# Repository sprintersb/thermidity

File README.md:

# Thermidity

AVR MCU based battery powered thermometer and hygrometer with e-ink display.  
Focus is on stable, accurate measurements and low power consumption. 
And of course on a nice, simple display.

The project is based on [avrink](https://github.com/gitdode/avrink) and uses the
following components:

* MCU AVR ATmega328P
* Thermistor NTC 100kΩ 0.1°C
* Humidity Sensor HIH-5030
* E-Ink display Adafruit Monochrome 2.13" 250x122
    * Driver SSD1680
    * SRAM 23K640
    * SD Card Reader (not used)
 
Thanks to https://github.com/sprintersb for helping me to improve the code and making it more efficient!

## Accuracy

AD conversion is done with 16x oversampling, yielding 12-bit virtual resolution 
with the 10-bit ADC, provided the signal contains some noise.

Each time measurements were taken, a moving average is updated which is used to 
calculate and display temperature, humidity and battery voltage.

A precision thermistor and precision low-voltage humidity sensor are used:

| Component  | Accuracy |
|------------|---------:|
| Thermistor |  ¹±0.1°C |
| HIH-5030   |    ±3%RH |

¹Series resistor 0.1% tolerance

## Power Consumption

Estimated average power consumption is about 90µA when measuring every 32 
seconds and updating the display once in about 5 minutes, hopefully giving an
operating time of at least 12 months with 3 AAA batteries (1100 mAh, 6% 
self-discharge). 

The consumption of each component at 3.8V and 22°C is about:

| Component  | Data Sheet | Measured |
|------------|-----------:|---------:|
| ATmega328P |     ¹4.2µA |    4.5µA |
| Thermistor |        N/A |     24µA |
| HIH-5030   |     ²200µA |    211µA |
| V-Divider  |        N/A |      2µA |
| Display    |       ³N/A |     14µA |

¹VCC = 3V, power-down sleep mode  
²VCC = 3.3V  
³Display in deep sleep mode + SRAM + SD Card Reader + Bus Transceiver  

Between taking measurements, the MCU is set to power-down sleep mode with the
watchdog used as wake-up source. Additionally, the thermistor and humidity 
sensor are powered off and between display updates, the display is set to deep 
sleep mode. Power consumption (measured) then is about 19µA at 3.8V for MCU 
and display.  

When measuring temperature, humidity and battery voltage in ADC noise reduction 
mode, consumption seems to be somewhere around 2mA for 6ms, plus a brief 
additional MCU awake period for updating the moving average with measured 
values. Before measuring, the sensors are powered on and given 100ms to settle, 
consuming about 240µA.

When updating the display, consumption is at around 6mA for about 3 seconds. 
Before that, the MCU has to calculate and format the average measurements and 
buffer the frame in SRAM.

The display is updated in fast update mode, taking 1.5s instead of 3s for full 
update mode, saving a considerable amount of power. To avoid ghosting effects, 
every 10th update is a full update.

When no measurement has changed, the display is not updated at all to extend its 
lifetime and to save more power.

Below the cutoff voltage of 3.0V, the watchdog is disabled to stop measuring and
updating the display, to at least delay total discharge of the batteries.
Consumption of the MCU then is at about 1µA and 19µA of the display.

The clock of unused modules TWI, all three timers and USART is switched off to 
reduce power consumption.

Disabling the ADC between measurements and the SPI between display updates both 
contributes to a significant reduction of power consumption. With an enabled SPI, 
consumption of the display including its peripheral is extremely unstable and 
varies between some tens of microamps and several milliamps. When driving the 
enable pin of the display low, consumption is stable at about 60µA. When not 
driving the enable pin low and disabling SPI (driving SCK pin low) consumption 
is at about 14µA.

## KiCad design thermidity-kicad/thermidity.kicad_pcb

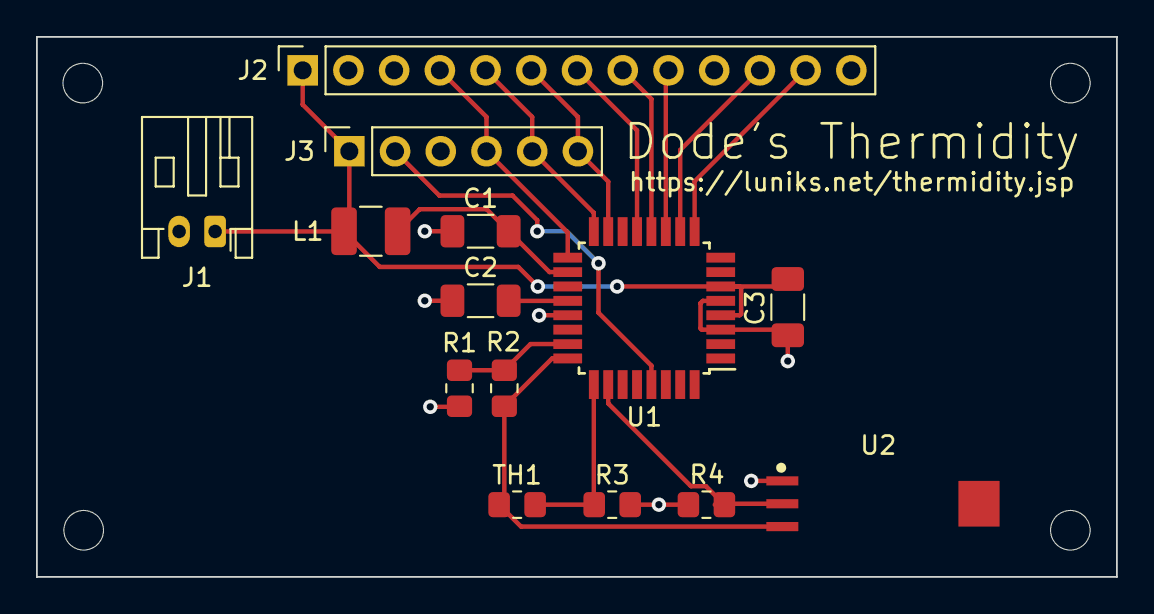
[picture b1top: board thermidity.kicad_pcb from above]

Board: 2 copper layers, 60.0 x 30.0 mm, 18 parts (0 on the bottom side), 16 nets.

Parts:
C1, C3: 100nF; C_1206_3216Metric_Pad1.33x1.80mm_HandSolder
C2: 1nF; C_1206_3216Metric_Pad1.33x1.80mm_HandSolder
H1, H2, H3, H4: M2; MountingHole_2.2mm_M2
J1: Battery; JST_PH_S2B-PH-K_1x02_P2.00mm_Horizontal
J2: Display; PinSocket_1x13_P2.54mm_Vertical
J3: ISP; PinSocket_1x06_P2.54mm_Vertical
L1: 10uH; L_1210_3225Metric_Pad1.42x2.65mm_HandSolder
R1: 300K; R_0805_2012Metric_Pad1.20x1.40mm_HandSolder
R2: 1.2M; R_0805_2012Metric_Pad1.20x1.40mm_HandSolder
R3: 100k 0.1%; R_0805_2012Metric_Pad1.20x1.40mm_HandSolder
R4: 65k; R_0805_2012Metric_Pad1.20x1.40mm_HandSolder
TH1: NTC 100k 0.1°C; R_0805_2012Metric_Pad1.20x1.40mm_HandSolder
U1: ATmega328P; TQFP-32_7x7mm_P0.8mm
U2: HIH-5030; HONEYWELL_HIH-5030-001

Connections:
+BATT: C3.2, J1.1, J2.1 (VIN), J3.1 (VCC), L1.1, U1.4 (VCC), U1.6 (VCC)
GND: C1.1, C2.1, C3.1, J1.2, J2.3 (GND), J3.3 (GND), R1.2, R3.2, R4.2, U1.3 (GND), U1.5 (GND), U1.21 (GND), U2.1 (-VE)
unnamed: C1.2, L1.2, U1.18 (AVCC)
unnamed: J2.4 (SCK), J3.4 (SCK), U1.17 (PB5)
unnamed: J2.5 (MISO), J3.5 (MISO), U1.16 (PB4)
unnamed: J2.6 (MOSI), J3.6 (MOSI), U1.15 (PB3)
unnamed: J2.7 (ECS), U1.13 (PB1)
unnamed: J2.8 (D/C), U1.12 (PB0)
unnamed: J2.9 (SRCS), U1.11 (PD7)
unnamed: J2.11 (RST), U1.10 (PD6)
unnamed: J2.12 (BUSY), U1.9 (PD5)
unnamed: J3.2 (RESET), U1.29 (~RESET/PC6)
unnamed: R1.1, R2.2, U1.23 (PC0)
unnamed: R2.1, TH1.1, U1.24 (PC1), U2.3 (+VE)
unnamed: R4.1, U1.26 (PC3), U2.2 (OUT)
unnamed: R3.1, TH1.2, U1.25 (PC2)

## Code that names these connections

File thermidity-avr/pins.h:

/* 
 * File:   pins.h
 * Author: torsten.roemer@luniks.net
 *
 * Created on 1. April 2023, 19:25
 */

#ifndef PINS_H
#define PINS_H

#include <avr/io.h>

/* Vref and Sensors */
#define DDR_SENS  DDRC
#define PORT_SENS PORTC
#define PIN_REF   PC0
#define PIN_TMP   PC2
#define PIN_RH    PC3
#define PIN_BAT   PC1

/* SPI */
#define DDR_SPI   DDRB
#define PORT_SPI  PORTB
#define PIN_SS    PB2
#define PIN_MOSI  PB3
#define PIN_MISO  PB4
#define PIN_SCK   PB5

/* SRAM */
#define DDR_SSPI  DDRD
#define PORT_SSPI PORTD
#define PIN_SRCS  PD7 // SRAM chip select

/* Display */
#define DDR_DSPI  DDRB
#define PORT_DSPI PORTB
#define PIN_ECS   PB1 // display chip select
#define PIN_DC    PB0 // display data/command

#define DDR_DISP  DDRD
#define PORT_DISP PORTD
#define PINP_DISP PIND
#define PIN_RST   PD6 // display reset
#define PIN_BUSY  PD5 // display busy

#endif /* PINS_H */

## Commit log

2023-05-04 add configurations.xml
2023-05-04 add build action and README.md
2023-05-04 improve rounding
2023-05-05 list components
2023-05-09 change and fix intervals of measuring and displaying values
2023-05-10 improve image quality
2023-05-12 improvements regarding measuring
    - measure more frequently
    - reduce weight of EWMA to 3:1
    - simplify update of EWMA
2023-05-14 do not update display when measurements did not change (#4)
2023-05-17 use 3.0V voltage reference for AREF, measure battery voltage (#6)
2023-05-17 use 3.0V voltage reference for AREF, measure battery voltage
2023-05-18 display a battery level symbol (#8)
2023-05-18 save power with watchdog: reduces from 7 to 1.1 mA, but still too much (#9)
    - use watchdog to wake up the controller every 8 seconds
    - set to power save mode
    - use ADC noise reduction mode for conversion
2023-05-18 fix comment
2023-05-18 allow some time to settle before making the first measurement
2023-05-18 wdt_reset() is not necessary
2023-05-18 improve bitmap
2023-05-19 stop the clock of unused modules to reduce power consumption
2023-05-21 move to subdir
2023-05-21 add FreeCAD subproject for frame
2023-05-21 add initial schematic
2023-05-21 move KiCad project
2023-05-21 move LICENSE and README.md
2023-05-21 move and adjust build.yml
2023-05-22 fix build.yml
2023-05-22 fix compiler warnings/notes
2023-05-22 remove 100nF cap from humidity sensor
2023-05-23 update schematic
2023-05-23 fix merge conflict
2023-05-23 use timer2 to wake up from power save mode (#11)
    - seems to consume less power than using watchdog
    - allows to be clocked by external watch crystal and use even less power
2023-05-23 formatting
2023-05-25 Power save mode with asynchronous timer2 clocked from external 32kHz watch crystal (#12)
    * use timer2 with external crystal - 0.6 mA, already quite good
    * disable ADC before going to sleep - saves another 200 uA
    * update README, add crystal to schematic
2023-05-25 fix typo
2023-05-29 improve circuit, update schematic, initial PCB, adjust pins
2023-05-31 Use watchdog to wake up MCU from sleep mode every second (#13)
    - avoids increasing current draw with 8 second interval
    - remove unnecessary checks
    - giving the ADC some time after sleep mode is not necessary
2023-05-31 minor schematic layout changes
2023-06-01 try to save some more power
    - use power-down sleep mode
    - stop timer2 clock as well
2023-06-01 update README, schematic + PCB (remove crystal)
2023-06-02 improve PCB, add comments
2023-06-02 improve README
2023-06-04 improve PCB
2023-06-04 trying to finalize...
2023-06-06 put back ground area and add vias for better connection
2023-06-06 use print instead of SMD for JST connector
2023-06-07 power off vref during idle time reducing consumption from 400uA to 43uA
    - power off vref including humidity sensor
    - add serial resistor to reduce charge current
    - fix pin initialization
2023-06-09 correct handling of variables > 8 bit shared between ISR and main execution path
2023-06-11 ratiometric measurement of humidity (#16)
    - removed voltage refererence
    - TMP36 to be replaced by thermistor (currently dependent on battery voltage)
    - battery voltage measurement should use internal 1.1 Vref (does not need to be accurate)
    - update schematic and README
    - update PCB
    - measure battery voltage using internal 1.1V reference
2023-06-11 remove the 1pF capacitor between AREF and GND
    - takes ~125us to discharge after switching from AVCC to internal 1.1 voltage reference and for the reference to settle
    - shouldn't be necessary and hopefully the 16x oversampling benefits from some noise
    - one part less
2023-06-13 Ratiometric measurement of temperature with a thermistor (#18)
    - replace TMP36 with a thermistor NTC 100k
    - put back 1nF cap between AREF and GND
    - wait 150us for the cap to discharge before converting with 1.1V reference
    - uint16_t is enough for 16x ADC
    - SMD footprint instead of TH for thermistor
    - calculate temperature
2023-06-14 avoid possible div/0 even if extremely unlikely
2023-06-15 cleanup comments
2023-06-15 update README and schematic + PCB
2023-06-15 fix comments
2023-06-15 adjust battery levels
    - display needs at least 3+V, so show empty below 3.2V
    - remove unused constant
2023-06-15 put more weight on average
2023-06-16 measured power consumption with a supercap capacitor
2023-06-17 set unused pins to defined level (enable pull-up) (#20)
2023-06-17 rename variable
2023-06-20 fine tuning
    - measure every 32 seconds (save power)
    - update display every 288 seconds (save power)
    - lower weight of the moving average (less inert)
    - set display to deep sleep mode 2 (save power)
2023-06-23 more infos about power consumption
2023-06-28 optimizations on battery usage (#21)
    - more fine grained display of display voltage
    - try to avoid discharging batteries below cutoff voltage
2023-07-02 pull not drive (input pin)
2023-07-03 add fast update mode, refactor and simplify (#22)
    - includes BOM
2023-07-05 read from SRAM in sequential mode when writing to display (#23)
2023-07-05 read from SRAM in sequential mode when writing to display
2023-07-09 update README, comment on modulo, add manual (German)
2023-07-12 update README and manual
2023-07-21 update manual
2023-07-30 disable SPI between display updates, fix schematic (#24)
    - fix high power consumption of display in sleep mode by disabling SPI (driving SCK low)
    - remove "unconnected" from MCU pin 20 (AREF) as it is connected
    - update README and manual
2023-07-30 disable SPI between display updates, fix schematic
    - fix high power consumption of display in sleep mode by disabling SPI (driving SCK low)
    - remove "unconnected" from MCU pin 20 (AREF) as it is connected
    - update README and manual
2023-07-30 add ISP header pin layout to manual
2023-08-01 add manual in English and French
2023-08-01 improve French translation
2023-08-04 keep ground plane away from mounting holes (#25)
2023-08-09 add drillholes to frame (#27)
2023-08-09 build with gcc 13 and avr-libc 2.1 (#26)
    - set --param=min-pagesize=0 to fix false warning "array subscript [0] is outside array bounds"
    (not for now to allow building also with avr-gcc 10)
    - adjust 'size' target
2023-09-05 Use flash addresses like "const __flash Font*" instead of passing around objects like "Font" that live in program memory. Local copies in static storage or on the stack are no more needed. Apart from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
    Compiles without warning with avr-gcc v8 when -Waddr-space-convert is active.
    Slight decrese in code size. Some comments might be out of sync.
    Qualifier "__flash" requires GNU-C99 or higher and avr-gcc v4.7 or
    newer. avr-gcc v4.7 was released in 2012.
    Notice that pgm_read_xxx(), memcpy_P etc. can still be used with
    flash addresses.
2023-09-05 Use flash addresses like "const __flash Font*" instead of passing (#29)
    around objects like "Font" that live in program memory. Local copies
    in static storage or on the stack are no more needed. Apart from that,
    removing requirement for pgm_read_xxx adds type-safety to variables that
    hold such pointers.
    Compiles without warning with avr-gcc v8 when -Waddr-space-convert is active.
    Slight decrese in code size. Some comments might be out of sync.
2023-09-06 Auto-generate lookup tables for unifont.c and dejavu.c. The generated lookup tables are included by these C files and pointed-to by new Font.code_to_id which has type const __flash uint8_t*. The auto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
    font.c::getGlyphAddress() uses the lookup table to speed to glyph lookup,
    provided font->code_to_id is availabvle -- which is always the case for now.
    This means that the linear lookup in getGlyphAddress() is actually dead code.
    The type of Font.code has been changed fro
2023-09-06 use binary instead of linear search (#30)
    use binary instead of linear search using algorithm from https://en.wikipedia.org/wiki/Binary_search_algorithm
2023-09-07 replace '-Wl,--relax' with '-mrelax' in Makefile
2023-09-08 add dependency on .h files and Makefile
2023-09-09 update project
    - set --param=min-pagesize=0
    - ugly hack in project configuration to avoid issues in code assistance with __flash qualifier
2023-09-09 update project
    - use self-hosted runner with avr-gcc 13.2.0
2023-09-09 remove unnecessary delays in display initialization (#36)
    - no need to wait 10ms since VCI already supplied, display is in deep sleep mode
    - no need to wait 100ms after hardware eset (waiting for busy) before software reset
    => might contribute to a tiny reduction of power consumption
2023-09-10 compile with -O2 instead of -Os as this seems to save a few microamps
2023-09-11 avoid frequent, expensive divisions (#37)
2023-09-13 Auto-generate lookup tables for unifont.c and dejavu.c. The generated lookup tables are included by these C files and pointed-to by the new field Font.code_to_id which has type const __flash uint8_t*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
    font.c::getGlyphAddress() uses the lookup table to speed up glyph lookup,
    provided font->code_to_id is non-NULL -- which is always the case for now.
    This means that the binary search in getGlyphAddress() is actually dead code.
    The type of Font.code has been changed from uint16_t to code_t, which
    makes it easier to switch char codes from a 16-bit type to an 8-bit type.
2023-09-14 Let watchdog wake up MCU only every 8 instead of 1 seconds, saving some power (#38)
    - set watchdog to bark every 8 seconds
    - counter can now be 8 instead of 16 bit - ATOMIC_BLOCK not needed
    - adjust constant and variable names
    - saves about 4uA in average power consumption
2023-09-17 More optimizations (#39)
    * use 'typedef uint8_t code_t' for char codes instead of uint16_t
    * use 'typedef uint8_t height_t' for bitmap height instead of uint16_t, same for width, row, col
    * optimize writing strings to and reading strings from SRAM (not used)
    * delay initial display update after power on (not necessary but avoids two consecutive display updates when connecting the programmer (display update starts almost immediately after power on and res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
2023-09-17 put shared types in 'types.h' (#40)
    * put shared types in 'types.h'
2023-09-17 fix typo, add types.h to Makefile
2023-09-17 add types.h to Makefile
2023-09-20 more optimizations on types (#41)
2023-09-20 set frame in SRAM sequential mode, saving more power (#43)
2023-10-06 make pointed-to objects const that are not supposed to be changed (#45)
2023-10-07 update NetBeans project configuration
2023-10-08 add STEP for whole frame, update PDF (#46)
2023-10-09 update to KiCad 7.0, add PDF for schematic and PCB (#47)
